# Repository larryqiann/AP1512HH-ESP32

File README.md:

## Note: This project was originally developed a long time ago and is being released to the public in archive form to document the hardware that has already been produced. Future updates to this project are not guaranteed, and future firmware and hardware development may not be backwards compatible with it. The hardware has not been thoroughly tested and as of this release, does not have firmware to correspond with the hardware yet. The contents of this repository are provided AS-IS where is, without any warranties or guarantees, express or implied. 

It is likely that there will have to be a Gen2 at some point.

# AP1512HH-ESP32
 Coway AP1512HH/AP-1512/AP 1512 Custom Main Board replacement with ESP32

 This is a custom, third party Main PCB (Development Kit) for the Coway AP1512HH air purifier and most likely, the different variants of this device. This project is intended for use with the *non-smart* versions of this device - the AP-1512HHS uses a board that natively supports wireless connectivity and I am unsure what the layout of this is like. This may be useful for developing an integration with Home Assistant or using ESPHome etc, but I have not developed such a firmware yet.

 **Please see the Teardown, along with its disussions, for general information about the device (https://github.com/device-teardowns/coway-ap1512hh)**

 The board is designed to use the same screw holes, dimensions, connectors, LED, and button placement in order to maximize compatibility and allow for drop in retrofit. It operates at entirely low isolated voltage because the power supply in the original unit provides this abstraction. 
 
 **Please note that despite this, please take precautions as the device was not designed with user access to the electronics in mind. Do not plug the unit in while connecting to the serial programming port, and avoid disassembling the power supply section. Use of this board will void the original regulatory approvals of the unit. This board has not been certified or evaluated to any safety, EMC, or other regulatory standards.**

## Getting Started

The easiest way to get started with the design is by reviewing the PDF schematics and layout, provided in the relevant folder. Some images of the board have been provided below as well.

## Hardware Overview

The PROG header on the board follows Espressif's recommended layout for the ESP-PROG interface. Please see the following for details: https://espressif-docs.readthedocs-hosted.com/projects/espressif-esp-iot-solution/en/latest/hw-reference/ESP-Prog_guide.html

The board integrates an ESP32-WROOM module on board. Many of the LEDs and switches are directly connected to GPIO pads of the chip, while a NPIC6C596 shift register is provided to drive the remaining LEDs. This shift register integrates a storage register to allow the LEDs to be updated all at once. An RGB LED is connected directly to the ESP32 to illuminate the dust sensor LED window. On-board 3.3V regulator, door switch detection, and fan PWM output and frequency feedback are implemented, along with level shift for direct interface with the PPD42 dust sensor.

## Safety Considerations

Use of this development board will void the original regulatory approvals of the unit. This board has not been certified or evaluated to any safety, EMC, or other regulatory standards. This board is intended for professional use by engineers or other qualified persons familiar with the safe operation and use of electrical lab and test equipment and safe working practices and is for development purposes only. This documentation, the hardware, and the design are provided for educational, development, and evaluation purposes only and are provided AS-IS with no guarantees or warranty, implied or stated.

Operation of the fan motor outside of its original specifications may cause it to malfunction, overheat, or pose risk of fire or electric shock. 

Operation of the fan outside of its original operating specifications i.e. at a higher than designed RPM may cause the blower wheel to explode or fragment. Some of these units have been documented to do this even on the original hardware and firmware configuration in Amazon reviews. While testing, always keep the blower case closed and the unit affixed to a stable surface and keep eyes, face, and body parts clear of the air outlet. 

Contact with the moving fan, fan motor, or high voltage components inside the case may cause personal injury or death. Never operate the unit with the case open, and never connect the board to a computer or other hardware while the power is plugged in. When disassembling the device, always discharge and verify zero voltage at all high voltage capacitors before touching any electrical components inside. 

## Misc. Hardware Notes

Here are some useful notes and information used for those developing firmware to be used with this development board:

The board mechanical layout is from scanning the original board using a flatbed scanner. The SVG and other info can be found in the Documentation folder. The board has been fit tested and fits great with the buttons and screw holes, as well as LEDs.

### Fan control

Fan control is accomplished through a two part interface:
1) A PWM output. This is, if I remember correctly, not a particularly high frequency interface. From the point of view of the ESP32, a good starting point would be to output 1000Hz. The power board internally uses an optocoupler to turn this PWM signal into an analog voltage with an RC filter for the motor, so it would be best to not pick too high or too low of a frequency here. The signal should not be audible because of this. In the original firmware, the lowest speed appears to be 20% and the highest 80%. **It is not necessarily advisable to use over 80%, as this may have been chosen to keep the DC bus ripple down, to limit the motor current, and/or to prevent overspeed of the fan wheel.** Either MCPWM or LEDC can be used to drive this output.

2) A PFM (pulse frequency modulation) input. This interface produces a square wave with constant 50% duty cycle (only transitions count - could be always positive or negative depending on motor position) to monitor the rotational speed of the motor. The motor will generate 6 pulses per revolution of the shaft (unlike most PC cooling fans which produce 2). Thus, the RPM can be easily determined by monitoring this pin. **It is strongly recommended to implement over-speed protection, locked rotor protection, and over/under load protection in the firmware.Ideally, the values may be measured using an oscilloscope prior to disassembly, and appropriate parameters selected.** I used to have these measurements but they have been lost, but I can recreate them sometime if there is demand. PID is a suitable method to perform motor control here - bearing in mind the limitations on the bandwidth of the feedback signal at low RPM. The MCPWM capture peripheral is well suited to this task.

### Peripheral control

The 15VEN_5V_OUT pin must be enabled for the fan motor to operate. 

The ION_5V_OUT pin toggles the relay that controls the ionizer of the unit

The door switch is connected to a GPIO on the ESP32 only and does not disable any functions in hardware directly

LED and button control is partially by NPIC6C596 power shift register and partially by direct GPIO control. Please refer to the schematic and the datasheet for this shift register to determine the firmware implementation.

### Dust sensor

The dust sensor originally used in the unit is a Shinyei PPD42. It uses the "Low Pulse Occupancy" method to detect the concentration of dust in the air (see https://aqicn.org/sensor/shinyei/). This type of sensor is not particularly accurate. A simple level shift is provided on board to use the sensor - you might consider using another channel of MCPWM Capture to trigger on this pin going low and cumulatively add the time within a certain period where the signal is LOW. As an alternative, the hardware can be modified to use a RC filter, and the value read from the ADC instead. However, this hardware solution has not been provided on the board.

### Connectors

The original connectors on the board are made by Yeonho (SMH series?). These are difficult to find. The closest replacements I found on LCSC are:

https://www.lcsc.com/product-detail/Wire-To-Board-Connector_DEALON-XHB-2AW_C2904999.html (2 pin, needs locking tab lightly shaved with utility knife)

https://www.lcsc.com/product-detail/Wire-To-Board-Connector_XFCN-M2501RF-06P_C492482.html (6 pin, power supply connector, no mods needed)

https://www.lcsc.com/product-detail/Wire-To-Board-Connector_XFCN-M2501RF-05P_C492481.html (5 pin, dust sensor, needs locking tab lightly shaved with utility knife)

## Thank you for reading the documentation! If you have any questions, feel free to open issues! Good luck on your development!

## License

CERN OHL v2 permissive (Please open issue if other is desired)

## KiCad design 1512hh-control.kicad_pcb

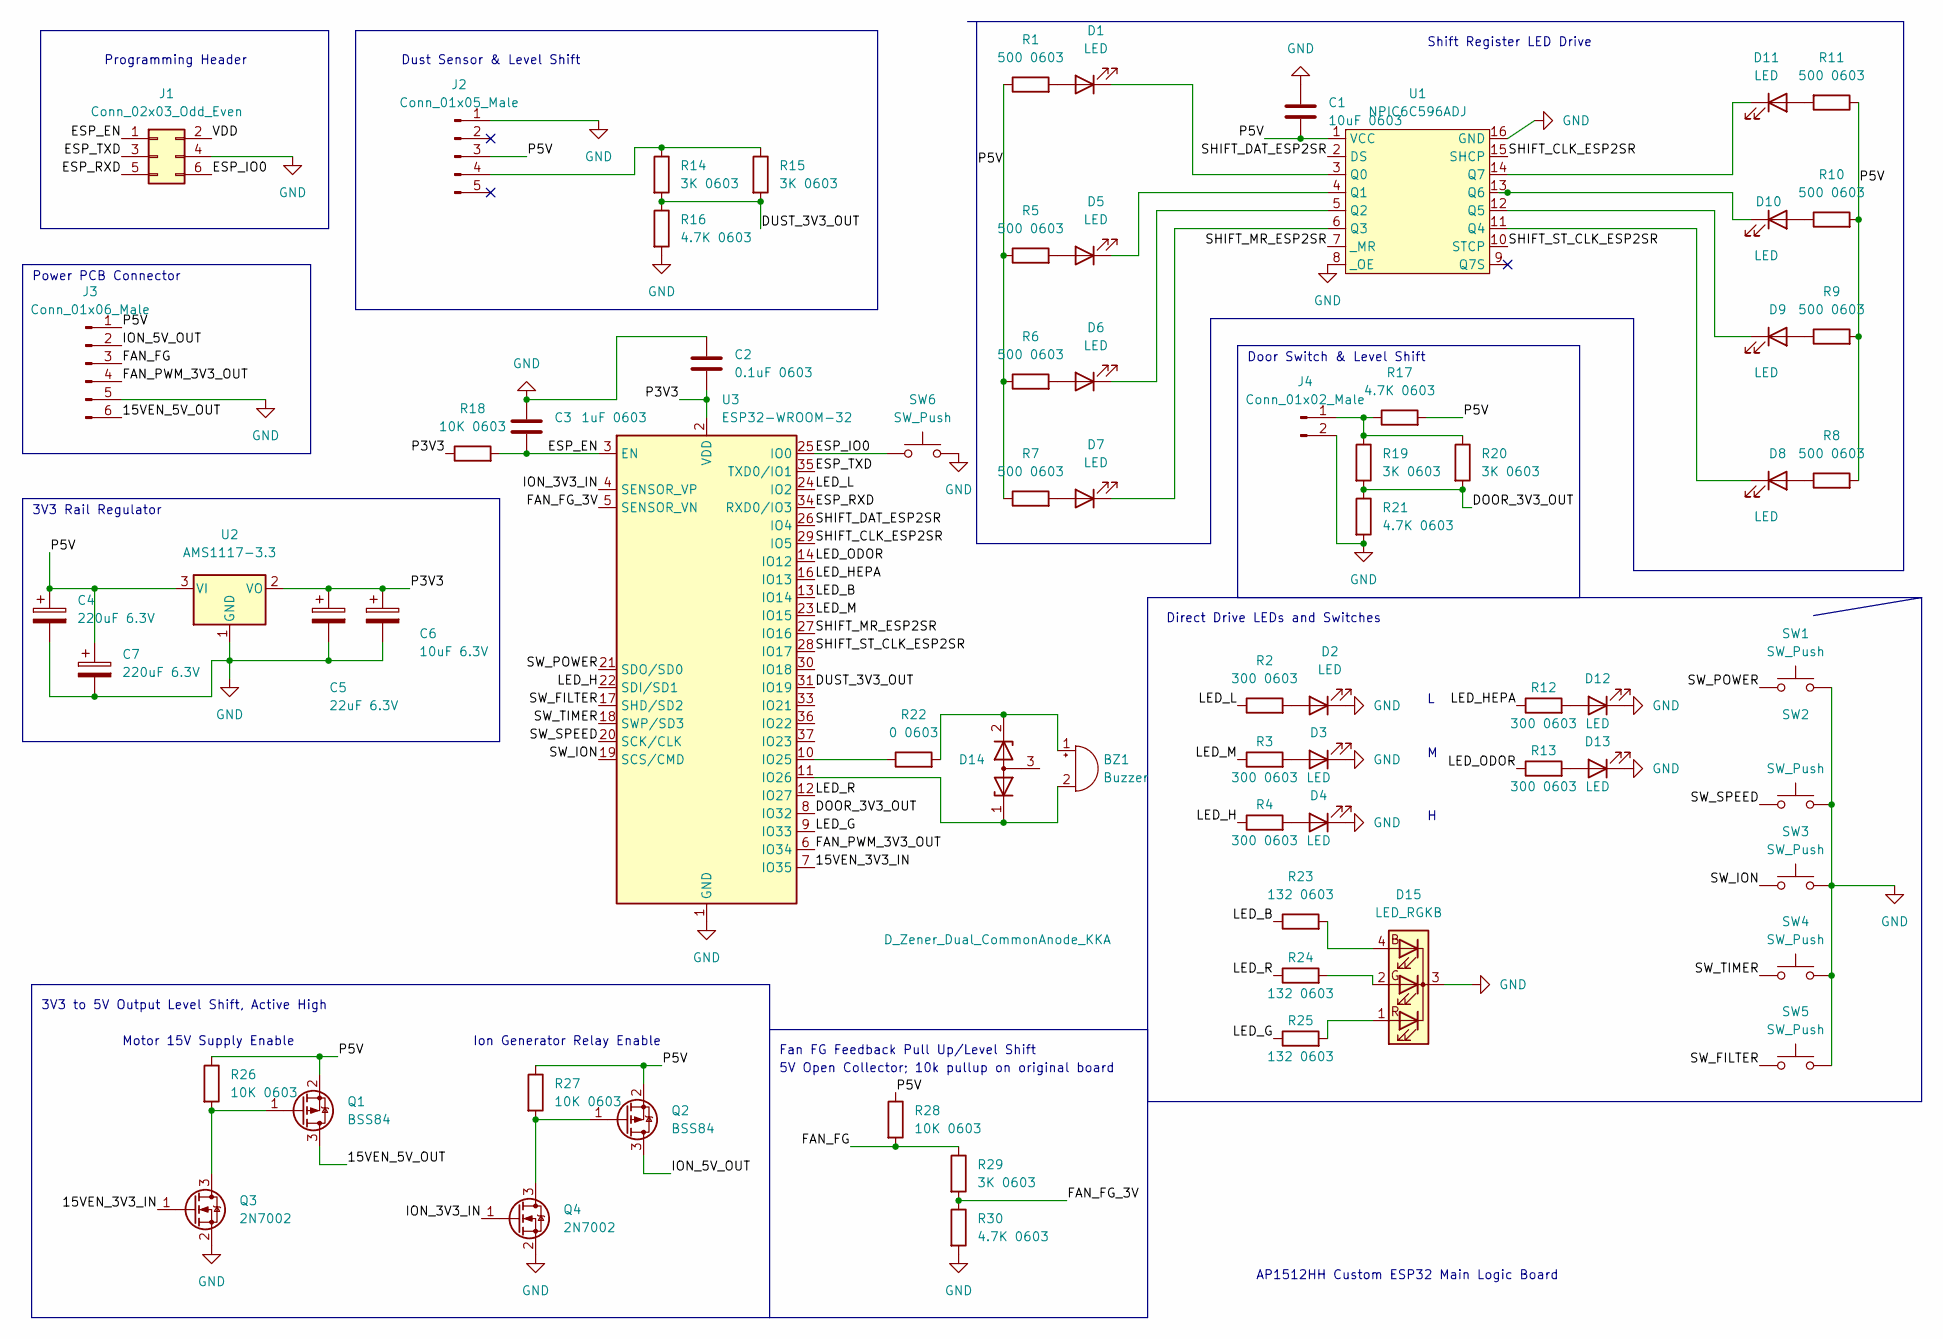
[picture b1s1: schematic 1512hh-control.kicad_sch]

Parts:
BZ1: Buzzer; PKM22EPPH4
C1: 10uF 0603; C_0603_1608Metric
C2: 0.1uF 0603; C_0603_1608Metric
C3: 1uF 0603; C_0603_1608Metric
C4, C7: 220uF 6.3V; C_Radial_D6.3mm_H11.0mm_P2.50mm
C5: 22uF 6.3V; C_Radial_D5.0mm_H11.0mm_P2.00mm
C6: 10uF 6.3V; C_Radial_D5.0mm_H11.0mm_P2.00mm
D1, D2, D3, D4, D5, D6, D7, D8, D9, D10, D11, D12, D13: LED; LED_D3.0mm
D14: D_Zener_Dual_CommonAnode_KKA; SOT-23
D15: LED_RGKB; LED_D5.0mm-4_RGB
J1: Conn_02x03_Odd_Even; PinHeader_2x03_P2.54mm_Vertical
J2: Conn_01x05_Male; JST_XH_S5B-XH-A-1_1x05_P2.50mm_Horizontal
J3: Conn_01x06_Male; JST_XH_S6B-XH-A-1_1x06_P2.50mm_Horizontal
J4: Conn_01x02_Male; JST_XH_S2B-XH-A-1_1x02_P2.50mm_Horizontal
Q1, Q2: BSS84; SOT-23
Q3, Q4: 2N7002; SOT-23
R1, R5, R6, R7, R8, R9, R10, R11: 500 0603; R_0603_1608Metric
R2, R3, R4, R12, R13: 300 0603; R_0603_1608Metric
R14, R15, R19, R20, R29: 3K 0603; R_0603_1608Metric
R16, R17, R21, R30: 4.7K 0603; R_0603_1608Metric
R18, R26, R27, R28: 10K 0603; R_0603_1608Metric
R22: 0 0603; R_0603_1608Metric
R23, R24, R25: 132 0603; R_0603_1608Metric
SW1, SW2, SW3, SW4, SW5, SW6: SW_Push; SW_PUSH_6mm_H5mm
U1: NPIC6C596ADJ; SOIC-16_3.9x9.9mm_P1.27mm
U2: AMS1117-3.3; SOT-223-3_TabPin2
U3: ESP32-WROOM-32

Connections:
/15VEN_3V3_IN: Q3.1 (G), U3.7 (IO35)
/15VEN_5V_OUT: J3.6, Q1.3 (D)
/DOOR_3V3_OUT: R19.2, R20.2, R21.1, U3.8 (IO32)
/DUST_3V3_OUT: R14.2, R15.2, R16.1, U3.31 (IO19)
/ESP_EN: C3.2, J1.1, R18.2, U3.3 (EN)
/ESP_IO0: J1.6, SW6.1, U3.25 (IO0)
/ESP_RXD: J1.5, U3.34 (RXD0/IO3)
/ESP_TXD: J1.3, U3.35 (TXD0/IO1)
/FAN_FG: J3.3, R28.2, R29.1
/FAN_FG_3V: R29.2, R30.1, U3.5 (SENSOR_VN)
/FAN_PWM_3V3_OUT: J3.4, U3.6 (IO34)
/ION_3V3_IN: Q4.1 (G), U3.4 (SENSOR_VP)
/ION_5V_OUT: J3.2, Q2.3 (D)
/LED_B: R23.1, U3.13 (IO14)
/LED_G: R25.1, U3.9 (IO33)
/LED_H: R4.1, U3.22 (SDI/SD1)
/LED_HEPA: R12.1, U3.16 (IO13)
/LED_L: R2.1, U3.24 (IO2)
/LED_M: R3.1, U3.23 (IO15)
/LED_ODOR: R13.1, U3.14 (IO12)
/LED_R: R24.1, U3.12 (IO27)
/P3V3: C2.2, C5.1, C6.1, R18.1, U2.2 (VO), U3.2 (VDD)
/P5V: C1.2, C4.1, C7.1, J2.3, J3.1, Q1.2 (S), Q2.2 (S), R1.1, R5.1, R6.1, R7.1, R8.2, R9.2, R10.2, R11.1, R17.2, R26.1, R27.1, R28.1, U1.1 (VCC), U2.3 (VI)
/SHIFT_CLK_ESP2SR: U1.15 (SHCP), U3.29 (IO5)
/SHIFT_DAT_ESP2SR: U1.2 (DS), U3.26 (IO4)
/SHIFT_MR_ESP2SR: U1.7 (_MR), U3.27 (IO16)
/SHIFT_ST_CLK_ESP2SR: U1.10 (STCP), U3.28 (IO17)
/SW_FILTER: SW5.1, U3.17 (SHD/SD2)
/SW_ION: SW3.1, U3.19 (SCS/CMD)
/SW_POWER: SW1.1, U3.21 (SDO/SD0)
/SW_SPEED: SW2.1, U3.20 (SCK/CLK)
/SW_TIMER: SW4.1, U3.18 (SWP/SD3)
/VDD: J1.2
GND: C1.1, C2.1, C3.1, C4.2, C5.2, C6.2, C7.2, D2.1 (K), D3.1 (K), D4.1 (K), D12.1 (K), D13.1 (K), D15.3 (K), J1.4, J2.1, J3.5, J4.2, Q3.2 (S), Q4.2 (S), R16.2, R21.2, R30.2, SW1.2, SW2.2, SW3.2, SW4.2, SW5.2, SW6.2, U1.8 (_OE), U1.16 (GND), U2.1 (GND), U3.1 (GND), U3.15 (GND), U3.38 (GND), U3.39 (GND)
unnamed: BZ1.1 (-), D14.2 (K), R22.2
unnamed: BZ1.2 (+), D14.1 (K), U3.11 (IO26)
unnamed: D1.1 (K), U1.3 (Q0)
unnamed: D1.2 (A), R1.2
unnamed: D2.2 (A), R2.2
unnamed: D3.2 (A), R3.2
unnamed: D4.2 (A), R4.2
unnamed: D5.1 (K), U1.4 (Q1)
unnamed: D6.1 (K), U1.5 (Q2)
unnamed: D7.1 (K), U1.6 (Q3)
unnamed: D8.1 (K), U1.11 (Q4)
unnamed: D9.1 (K), U1.12 (Q5)
unnamed: D9.2 (A), R9.1
unnamed: D10.1 (K), U1.13 (Q6)
unnamed: D10.2 (A), R10.1
unnamed: D11.1 (K), U1.14 (Q7)
unnamed: D11.2 (A), R11.2
unnamed: D12.2 (A), R12.2
unnamed: D13.2 (A), R13.2
unnamed: D15.1 (RA), R25.2
unnamed: D15.2 (GA), R24.2
unnamed: D15.4 (BA), R23.2
unnamed: J2.4, R14.1, R15.1
unnamed: J4.1, R17.1, R19.1, R20.1
unnamed: Q1.1 (G), Q3.3 (D), R26.2
unnamed: Q2.1 (G), Q4.3 (D), R27.2
unnamed: D5.2 (A), R5.2
unnamed: D6.2 (A), R6.2
unnamed: D7.2 (A), R7.2
unnamed: D8.2 (A), R8.1
unnamed: R22.1, U3.10 (IO25)

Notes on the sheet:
Dust Sensor & Level Shift
Fan FG Feedback Pull Up/Level Shift
5V Open Collector; 10k pullup on original board
3V3 to 5V Output Level Shift, Active High
Power PCB Connector
3V3 Rail Regulator
Ion Generator Relay Enable
Door Switch & Level Shift
Shift Register LED Drive
Programming Header
Direct Drive LEDs and Switches
Motor 15V Supply Enable
AP1512HH Custom ESP32 Main Logic Board

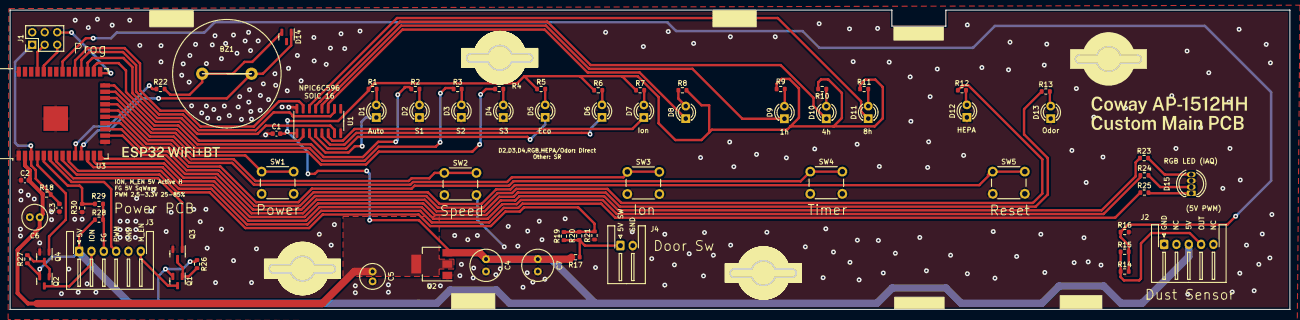
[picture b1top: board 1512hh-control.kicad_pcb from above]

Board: 2 copper layers, 259.5 x 60.7 mm, 69 parts (0 on the bottom side), 64 nets.

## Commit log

2022-01-20 Add files
2022-01-22 Route and layout board
2024-06-03 Add documentation for public release
2024-06-03 Add LICENSE
